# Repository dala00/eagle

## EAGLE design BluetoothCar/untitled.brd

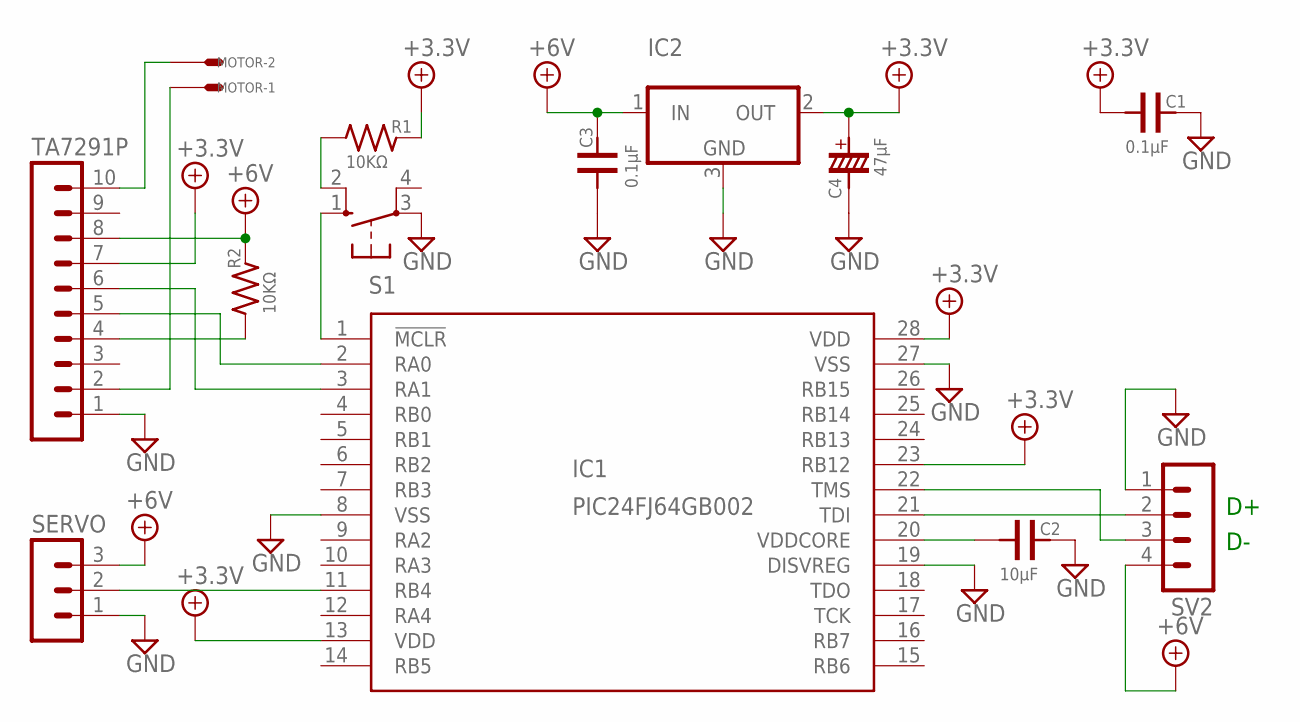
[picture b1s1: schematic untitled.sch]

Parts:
C1, C3: 0.1μF; C25-25X44
C2: 10μF; C25-25X44
C4: 47μF; TT2D5L
IC1: PIC24FJ64GB002; DIL28-3
IC2: TA48MV; HSIP3-P2.30B/V
MOTOR: CON2S; CON2
R1, R2: 10KΩ; 0204/5
S1: 10-XX; B3F-10XX
SERVO: MA03-1
SV2: MA04-1
TA7291P: MA10-1

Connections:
+4.1V: C1.P$1 (1), C4.P$1, IC1.13 (VDD), IC1.23 (RB12), IC1.28 (VDD), IC2.2 (OUT), R1.2, TA7291P.7
+5V: C3.P$2 (2), IC2.1 (IN), R2.2, SERVO.3, SV2.4, TA7291P.8
GND: C1.P$2 (2), C2.P$2 (2), C3.P$1 (1), C4.P$2, IC1.8 (VSS), IC1.19 (DISVREG), IC1.27 (VSS), IC2.3 (GND), S1.3, SERVO.1, SV2.1, TA7291P.1
unnamed: IC1.11 (RB4), SERVO.2
unnamed: R1.1, S1.2 (S1)
unnamed: IC1.1 (!MCLR), S1.1 (S)
unnamed: C2.P$1 (1), IC1.20 (VDDCORE)
unnamed: IC1.21 (TDI), SV2.2
unnamed: IC1.22 (TMS), SV2.3
unnamed: R2.1, TA7291P.4
unnamed: IC1.2 (RA0), TA7291P.5
unnamed: IC1.3 (RA1), TA7291P.6
unnamed: MOTOR.P$1, TA7291P.2
unnamed: MOTOR.P$2, TA7291P.10

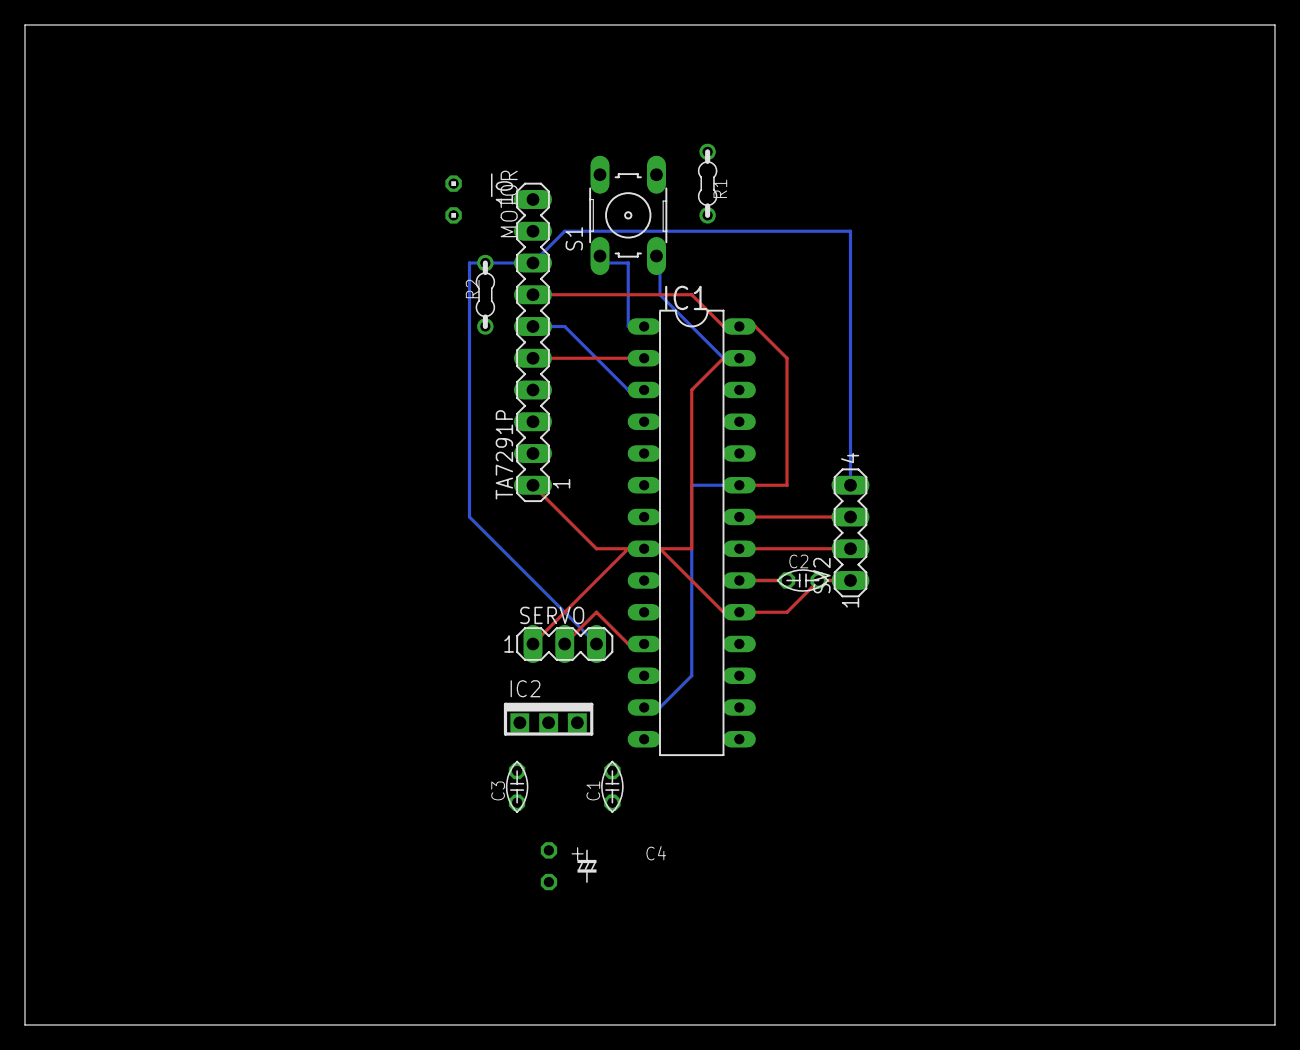
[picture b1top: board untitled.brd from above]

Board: 2 copper layers, 100.0 x 80.0 mm, 13 parts (0 on the bottom side), 14 nets.

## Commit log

2014-12-29 first comit
